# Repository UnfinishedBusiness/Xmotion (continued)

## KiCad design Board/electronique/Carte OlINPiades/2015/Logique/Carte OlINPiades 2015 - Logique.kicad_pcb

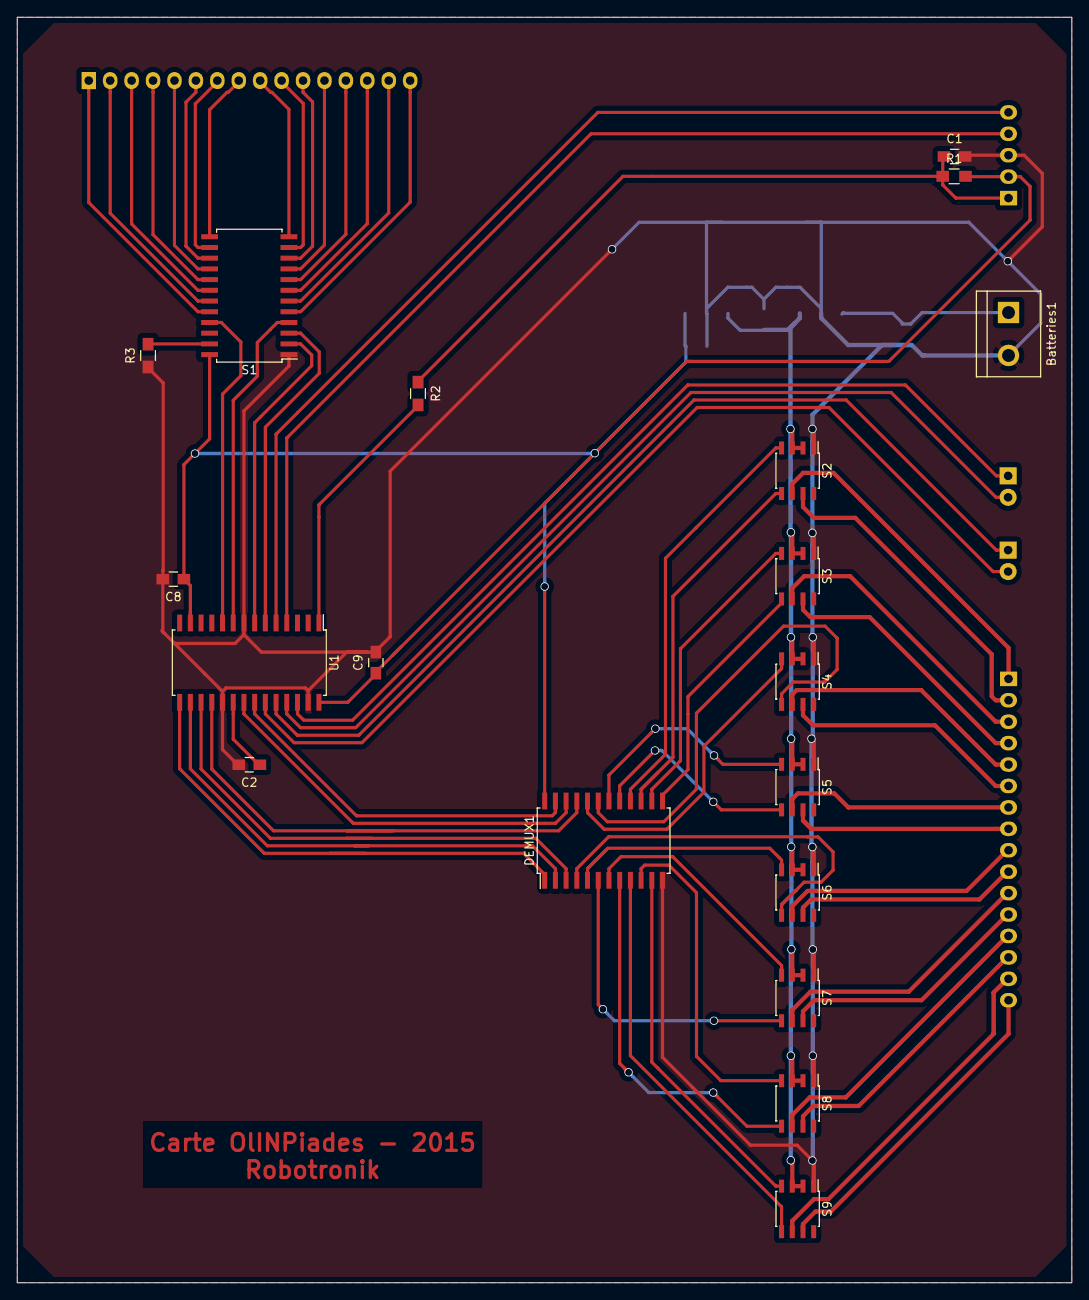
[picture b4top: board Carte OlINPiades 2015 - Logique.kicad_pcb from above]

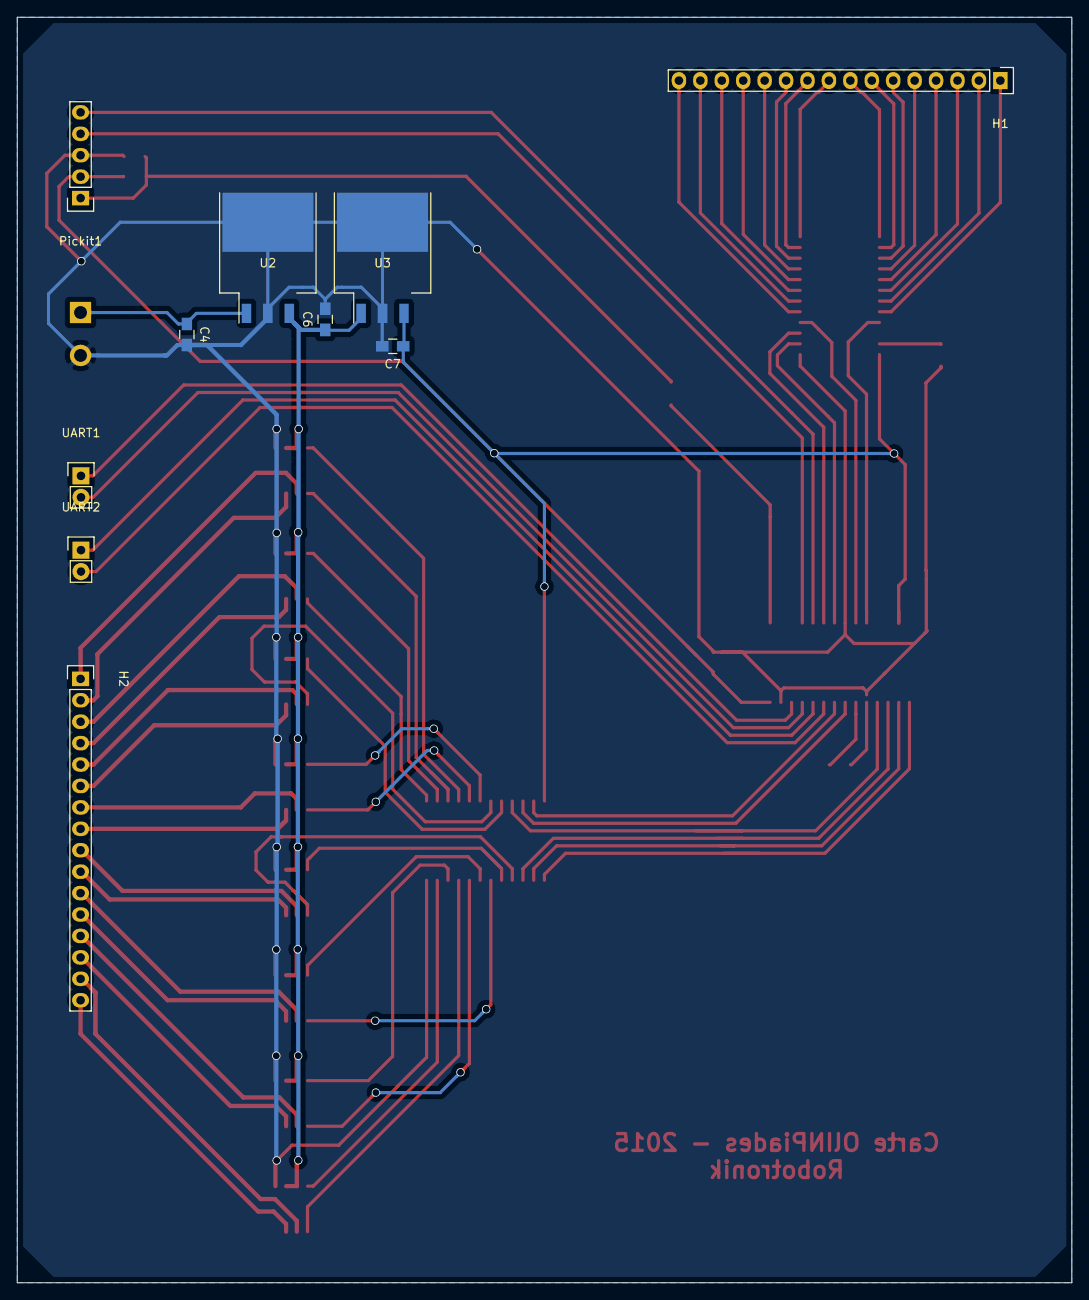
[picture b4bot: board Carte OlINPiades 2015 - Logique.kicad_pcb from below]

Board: 2 copper layers, 125.0 x 150.0 mm, 29 parts (10 on the bottom side), 72 nets.

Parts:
Batteries1: CONN_2; bornier2
C1, C6: 100nF; C_0805_HandSoldering
C2, C7: 10uF; C_0805_HandSoldering
C4: 330nF; C_0805_HandSoldering
C8, C9: 0,1uF; C_0805_HandSoldering
DEMUX1: 74HC4514; SOIC-24_7.5x15.4mm_Pitch1.27mm
H1, H2: PinHeader; Socket_Strip_Straight_1x16
Pickit1: CONN_5; Pin_Header_Straight_1x05
R1: 10kOhm; R_0805_HandSoldering
R2: 470Ohm; R_0805_HandSoldering
R3: TODO; R_0805_HandSoldering
S1: CAT4016; SOIC-24_7.5x15.4mm_Pitch1.27mm
S2, S3, S4, S5, S6, S7, S8, S9: TPS2080; SOIC-8_3.9x4.9mm_Pitch1.27mm
U1: dsPIC33FJ128MC802; SOIC-28_7.5x17.9mm_Pitch1.27mm
U2: 7805; TO-263
U3: LM2937-3.3; TO-263
UART1, UART2: CONN_2; Pin_Header_Straight_1x02

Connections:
+3.3V: C7.1, C8.1, C9.1, DEMUX1.24, Pickit1.2, R1.2, S1.24, U1.13, U1.28, U3.VO
+5V: C6.1, S2.2, S2.3, S3.2, S3.3, S4.2, S4.3, S5.2, S5.3, S6.2, S6.3, S7.2, S7.3, S8.2, S8.3, S9.2, S9.3, U2.VO, U3.VI
+12V: Batteries1.1, C4.1, U2.VI
GND: Batteries1.2, C1.2, C2.2, C4.2, C6.2, C7.2, C8.2, C9.2, DEMUX1.12, Pickit1.3, R3.1, S1.1, S2.1, S3.1, S4.1, S5.1, S6.1, S7.1, S8.1, S9.1, U1.8, U1.19, U1.27, U2.GND, U3.GND
unnamed: C1.1, Pickit1.1, R1.1, R2.1
unnamed: C2.1, U1.20
unnamed: DEMUX1.4, S6.5
unnamed: DEMUX1.5, S6.4
unnamed: DEMUX1.6, S7.5
unnamed: DEMUX1.7, S7.4
unnamed: DEMUX1.8, S8.5
unnamed: DEMUX1.9, S9.5
unnamed: DEMUX1.10, S8.4
unnamed: DEMUX1.11, S9.4
unnamed: DEMUX1.13, S3.5
unnamed: DEMUX1.14, S3.4
unnamed: DEMUX1.15, S2.5
unnamed: DEMUX1.16, S2.4
unnamed: DEMUX1.17, S5.5
unnamed: DEMUX1.18, S5.4
unnamed: DEMUX1.19, S4.5
unnamed: DEMUX1.20, S4.4
unnamed: H1.1, S1.20
unnamed: H1.2, S1.19
unnamed: H1.3, S1.18
unnamed: H1.4, S1.17
unnamed: H1.5, S1.16
unnamed: H1.6, S1.15
unnamed: H1.7, S1.14
unnamed: H1.8, S1.13
unnamed: H1.9, S1.12
unnamed: H1.10, S1.11
unnamed: H1.11, S1.10
unnamed: H1.12, S1.9
unnamed: H1.13, S1.8
unnamed: H1.14, S1.7
unnamed: H1.15, S1.6
unnamed: H1.16, S1.5
unnamed: H2.1, S2.6
unnamed: H2.2, S2.7
unnamed: H2.3, S3.6
unnamed: H2.4, S3.7
unnamed: H2.5, S4.6
unnamed: H2.6, S4.7
unnamed: H2.7, S5.6
unnamed: H2.8, S5.7
unnamed: H2.9, S6.6
unnamed: H2.10, S6.7
unnamed: H2.11, S7.6
unnamed: H2.12, S7.7
unnamed: H2.13, S8.6
unnamed: H2.14, S8.7
unnamed: H2.15, S9.6
unnamed: H2.16, S9.7
unnamed: R2.2, U1.1
unnamed: R3.2, S1.23
PGC: Pickit1.5, U1.5
PGD: Pickit1.4, U1.4
RA2: S1.4, U1.9
RA3: S1.21, U1.10
RB2: S1.3, U1.6
RB3: S1.2, U1.7
RB6: DEMUX1.1, U1.15
RB7: DEMUX1.2, U1.16
RB8: DEMUX1.3, U1.17
RB9: DEMUX1.21, U1.18
RB10: DEMUX1.22, U1.21
RB11: DEMUX1.23, U1.22
RB12: U1.23, UART2.2
RB13: U1.24, UART2.1
RB14: U1.25, UART1.2
RB15: U1.26, UART1.1

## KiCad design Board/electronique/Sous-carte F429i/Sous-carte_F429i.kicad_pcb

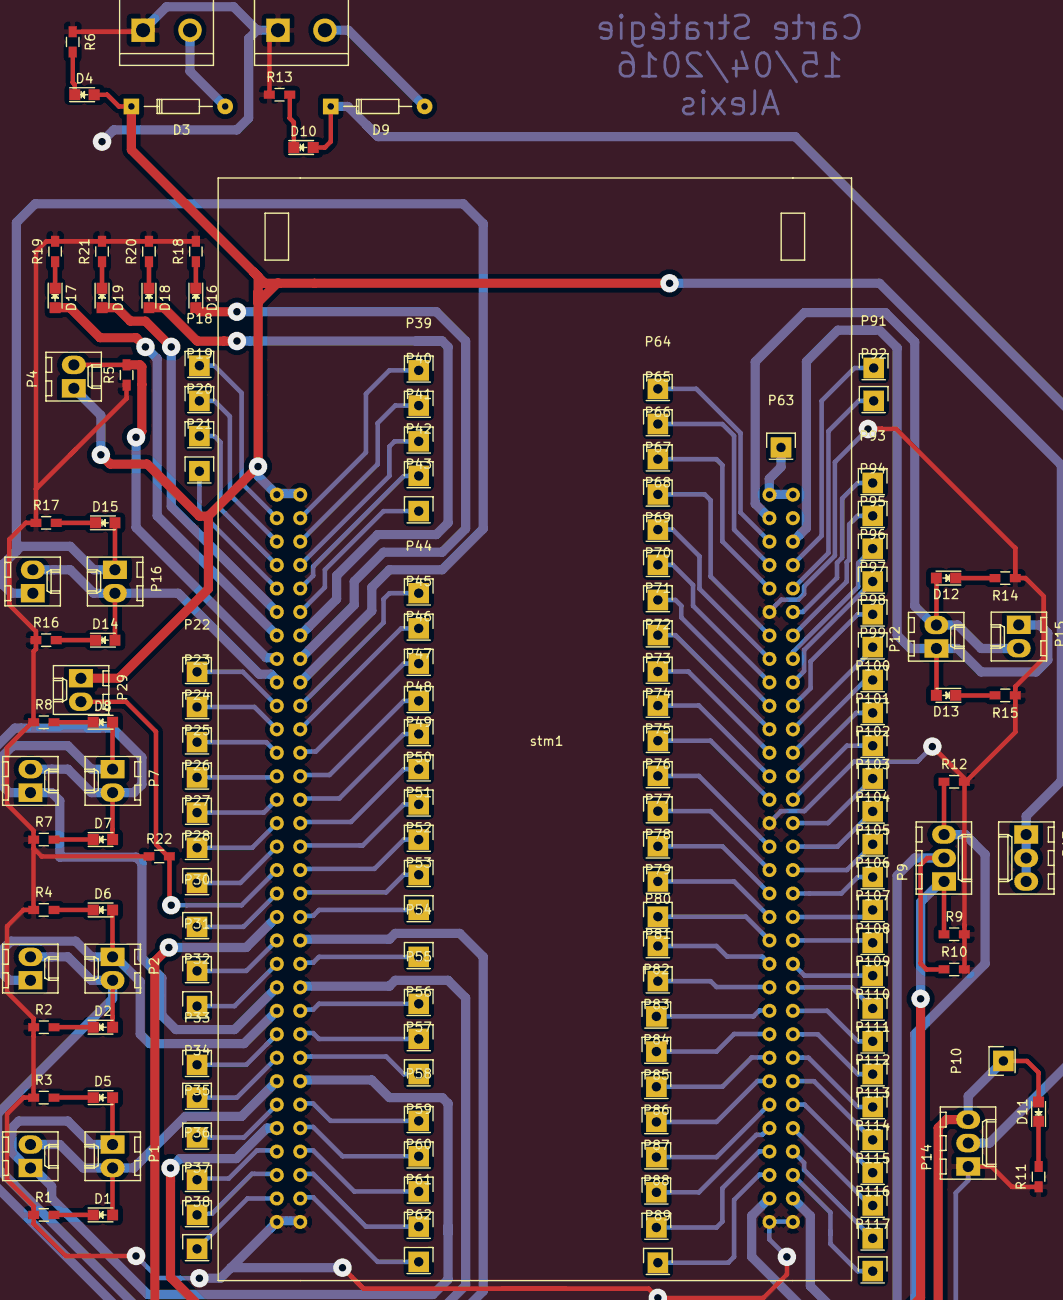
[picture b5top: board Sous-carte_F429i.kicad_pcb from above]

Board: 2 copper layers, 158 parts (0 on the bottom side), 140 nets.

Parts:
D1, D2, D4, D5, D6, D7, D8, D10, D11, D12, D13, D14, D15, D16, D17, D18, D19: LED; LED_0805
D3, D9: D; Diode_DO-35_SOD27_Horizontal_RM10
P1, P2, P4, P5, P6, P7, P8, P12, P15, P16, P17, P29: CONN_01X02; Molex_KK_6410-02
P3, P11: CONN_01X02; bornier2
P9, P13, P14: CONN_01X03; Molex_KK_6410-03
P10, P18, P19, P20, P21, P22, P23, P24, P25, P26, P27, P28, P30, P31, P32, P33, P34, P35, P36, P37, P38, P39, P40, P41, P42, P43, P44, P45, P46, P47, P48, P49, P50, P51, P52, P53, P54, P55, P56, P57, P58, P59, P60, P61, P62, P63, P64, P65, P66, P67, P68, P69, P70, P71, P72, P73, P74, P75, P76, P77, P78, P79, P80, P81, P82, P83, P84, P85, P86, P87, P88, P89, P91, P92, P93, P94, P95, P96, P97, P98, P99, P100, P101, P102, P103, P104, P105, P106, P107, P108, P109, P110, P111, P112, P113, P114, P115, P116, P117: CONN_01X01; Pin_Header_Straight_1x01
R1, R2, R3, R4, R5, R6, R7, R8, R9, R10, R11, R12, R13, R14, R15, R16, R17, R18, R19, R20, R21, R22: R; R_0603_HandSoldering
stm1: STM32F429i-Discovery; stm32f429i-disco

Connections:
+5V: D3.1, D4.2, P4.1, P13.1, P13.2, P13.3, P29.1, stm1.1, stm1.2
+BATT: D9.1, D10.2, P14.2
EQUIPE: P29.2, R22.2, stm1.33
GND: P3.1, P11.1, P14.1, R1.1, R2.1, R3.1, R4.1, R5.1, R6.1, R7.1, R8.1, R9.2, R10.2, R11.1, R12.2, R13.1, R14.1, R15.1, R16.1, R17.1, R18.2, R19.2, R20.2, R21.2, R22.1, stm1.63, stm1.64, stm1.75, stm1.93, stm1.127, stm1.128
LED_1: D16.2, stm1.16
LED_2: D17.2, stm1.13
LED_3: D18.2, stm1.14
LED_4: D19.2, stm1.11
unnamed: D1.1, R1.2
unnamed: D2.1, R2.2
unnamed: D3.2, P3.2
unnamed: D4.1, R6.2
unnamed: D5.1, R3.2
unnamed: D6.1, R4.2
unnamed: D7.1, R7.2
unnamed: D8.1, R8.2
unnamed: D9.2, P11.2
unnamed: D10.1, R13.2
unnamed: D11.1, R11.2
unnamed: D12.1, R14.2
unnamed: D13.1, R15.2
unnamed: D14.1, R16.2
unnamed: D15.1, R17.2
unnamed: D16.1, R18.1
unnamed: D17.1, R19.1
unnamed: D18.1, R20.1
unnamed: D19.1, R21.1
unnamed: P18.1, stm1.3
unnamed: P19.1, stm1.5
unnamed: P20.1, stm1.7
unnamed: P21.1, stm1.9
unnamed: P22.1, stm1.19
unnamed: P23.1, stm1.21
unnamed: P24.1, stm1.23
unnamed: P25.1, stm1.25
unnamed: P26.1, stm1.27
unnamed: P27.1, stm1.29
unnamed: P28.1, stm1.31
unnamed: P30.1, stm1.35
unnamed: P31.1, stm1.39
unnamed: P32.1, stm1.41
unnamed: P33.1, stm1.47
unnamed: P34.1, stm1.49
unnamed: P35.1, stm1.53
unnamed: P36.1, stm1.57
unnamed: P37.1, stm1.59
unnamed: P38.1, stm1.61
unnamed: P39.1, stm1.4
unnamed: P40.1, stm1.6
unnamed: P41.1, stm1.8
unnamed: P42.1, stm1.10
unnamed: P43.1, stm1.12
unnamed: P44.1, stm1.20
unnamed: P45.1, stm1.22
unnamed: P46.1, stm1.24
unnamed: P47.1, stm1.26
unnamed: P48.1, stm1.28
unnamed: P49.1, stm1.30
unnamed: P50.1, stm1.32
unnamed: P51.1, stm1.34
unnamed: P52.1, stm1.36
unnamed: P53.1, stm1.38
unnamed: P54.1, stm1.42
unnamed: P55.1, stm1.46
unnamed: P56.1, stm1.48
unnamed: P57.1, stm1.50
unnamed: P58.1, stm1.54
unnamed: P59.1, stm1.56
unnamed: P60.1, stm1.58
unnamed: P61.1, stm1.60
unnamed: P62.1, stm1.62
unnamed: P63.1, stm1.65, stm1.66
unnamed: P64.1, stm1.69
unnamed: P65.1, stm1.71
unnamed: P66.1, stm1.73
unnamed: P67.1, stm1.77
unnamed: P68.1, stm1.79
unnamed: P69.1, stm1.81
unnamed: P70.1, stm1.83
unnamed: P71.1, stm1.85
unnamed: P72.1, stm1.87
unnamed: P73.1, stm1.89
unnamed: P74.1, stm1.91
unnamed: P75.1, stm1.95
unnamed: P76.1, stm1.97
unnamed: P77.1, stm1.99
unnamed: P78.1, stm1.101
unnamed: P79.1, stm1.103
unnamed: P80.1, stm1.105
unnamed: P81.1, stm1.107
unnamed: P82.1, stm1.109
unnamed: P83.1, stm1.111
unnamed: P84.1, stm1.113
unnamed: P85.1, stm1.115
unnamed: P86.1, stm1.117
unnamed: P87.1, stm1.119
unnamed: P88.1, stm1.121
unnamed: P89.1, stm1.123
unnamed: P91.1, stm1.72
unnamed: P92.1, stm1.74
unnamed: P93.1, stm1.76
unnamed: P94.1, stm1.78
unnamed: P95.1, stm1.80
unnamed: P96.1, stm1.82
unnamed: P97.1, stm1.84
unnamed: P98.1, stm1.86
unnamed: P99.1, stm1.88
unnamed: P100.1, stm1.90
unnamed: P101.1, stm1.92
unnamed: P102.1, stm1.94
unnamed: P103.1, stm1.96
unnamed: P104.1, stm1.98
unnamed: P105.1, stm1.100
unnamed: P106.1, stm1.102
unnamed: P107.1, stm1.104
unnamed: P108.1, stm1.106
unnamed: P109.1, stm1.108
unnamed: P110.1, stm1.110
unnamed: P111.1, stm1.112
unnamed: P112.1, stm1.114
unnamed: P113.1, stm1.116
unnamed: P114.1, stm1.118
unnamed: P115.1, stm1.120
unnamed: P116.1, stm1.122
unnamed: P117.1, stm1.124
START: P4.2, R5.2, stm1.15
SWITCH_0: P9.1, R9.1, stm1.55
SWITCH_1: P9.2, R10.1, stm1.126
SWITCH_2: P9.3, R12.1, stm1.125
UART4_RX: D2.2, P2.2, P6.2, stm1.44
UART4_TX: D6.2, P2.1, P6.1, stm1.45
UART5_RX: D7.2, P7.2, P8.2, stm1.40
UART5_TX: D8.2, P7.1, P8.1, stm1.43
UART7_RX: D12.2, P12.2, P15.2, stm1.67
UART7_TX: D13.2, P12.1, P15.1, stm1.70
UART8_RX: D14.2, P16.2, P17.2, stm1.17
UART8_TX: D15.2, P16.1, P17.1, stm1.18
USART1_RX: D1.2, P1.2, P5.2, stm1.51
USART1_TX: D5.2, P1.1, P5.1, stm1.52
USART2_TX: D11.2, P10.1, P14.3, stm1.37

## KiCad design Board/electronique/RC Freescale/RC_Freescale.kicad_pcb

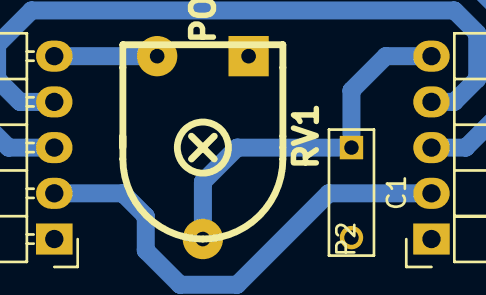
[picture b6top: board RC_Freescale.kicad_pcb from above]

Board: 2 copper layers, 4 parts (0 on the bottom side), 6 nets.

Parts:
C1: C; C_Rect_L7_W2.5_P5
P1: CONN_01X05; Pin_Header_Angled_1x05
P2: CONN_01X05; Socket_Strip_Angled_1x05
RV1: POT; POAH

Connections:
/2: P1.2, P2.2
/3: P1.3, P2.3
/4: P1.4, P2.4
GND: C1.2, P1.1, P2.1
unnamed: C1.1, P2.5, RV1.2
unnamed: P1.5, RV1.3

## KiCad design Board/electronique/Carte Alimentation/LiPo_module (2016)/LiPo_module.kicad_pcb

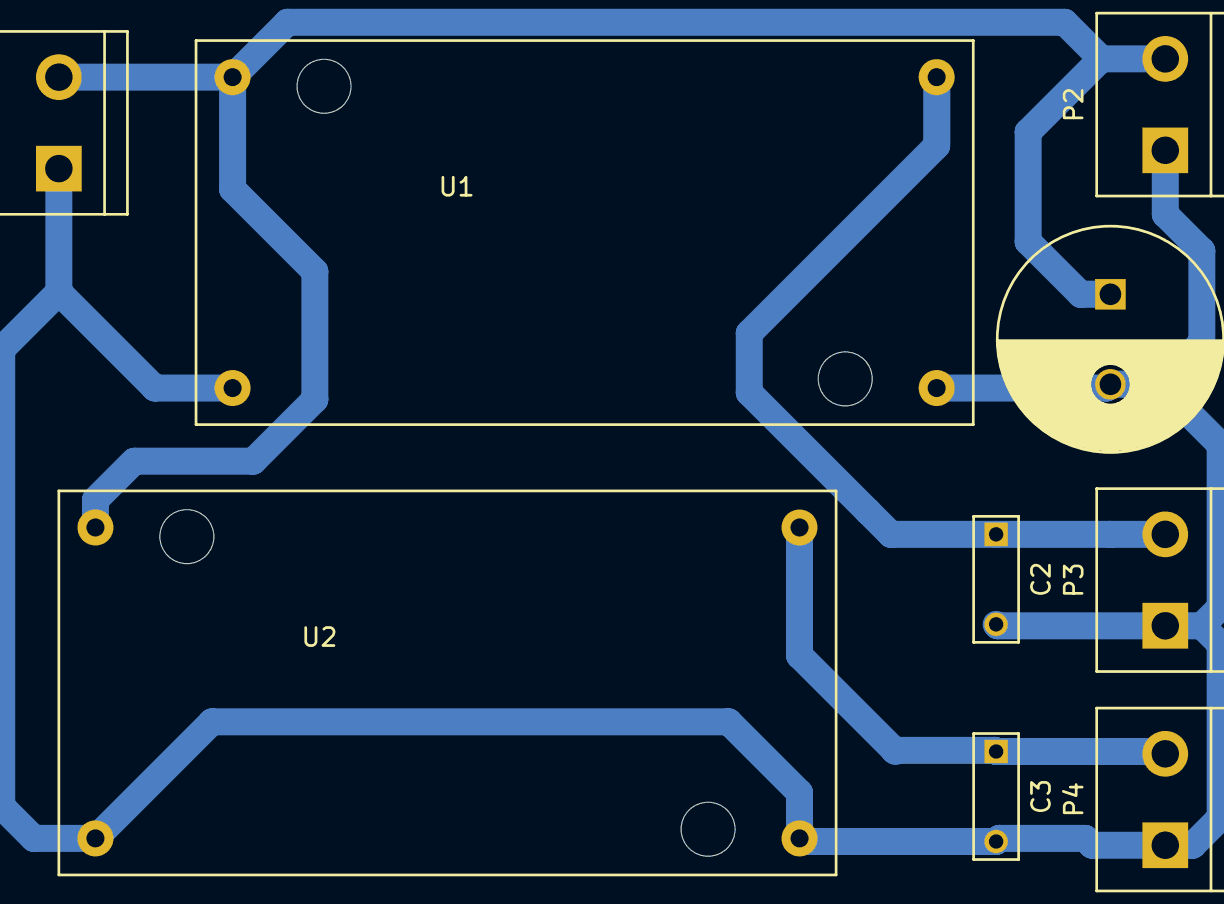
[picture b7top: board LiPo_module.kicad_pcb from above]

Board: 2 copper layers, 9 parts (0 on the bottom side), 4 nets.

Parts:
C1: CP; C_Radial_D12.5_L25_P5
C2, C3: C; C_Rect_L7_W2.5_P5
P1, P2, P3, P4: CONN_01X02; bornier2
U1, U2: DSN2596

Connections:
GND: C1.2, C2.2, C3.2, P1.1, P2.1, P3.1, P4.1, U1.2, U1.3, U2.2, U2.3
unnamed: C1.1, P1.2, P2.2, U1.1, U2.1
unnamed: C2.1, P3.2, U1.4
unnamed: C3.1, P4.2, U2.4

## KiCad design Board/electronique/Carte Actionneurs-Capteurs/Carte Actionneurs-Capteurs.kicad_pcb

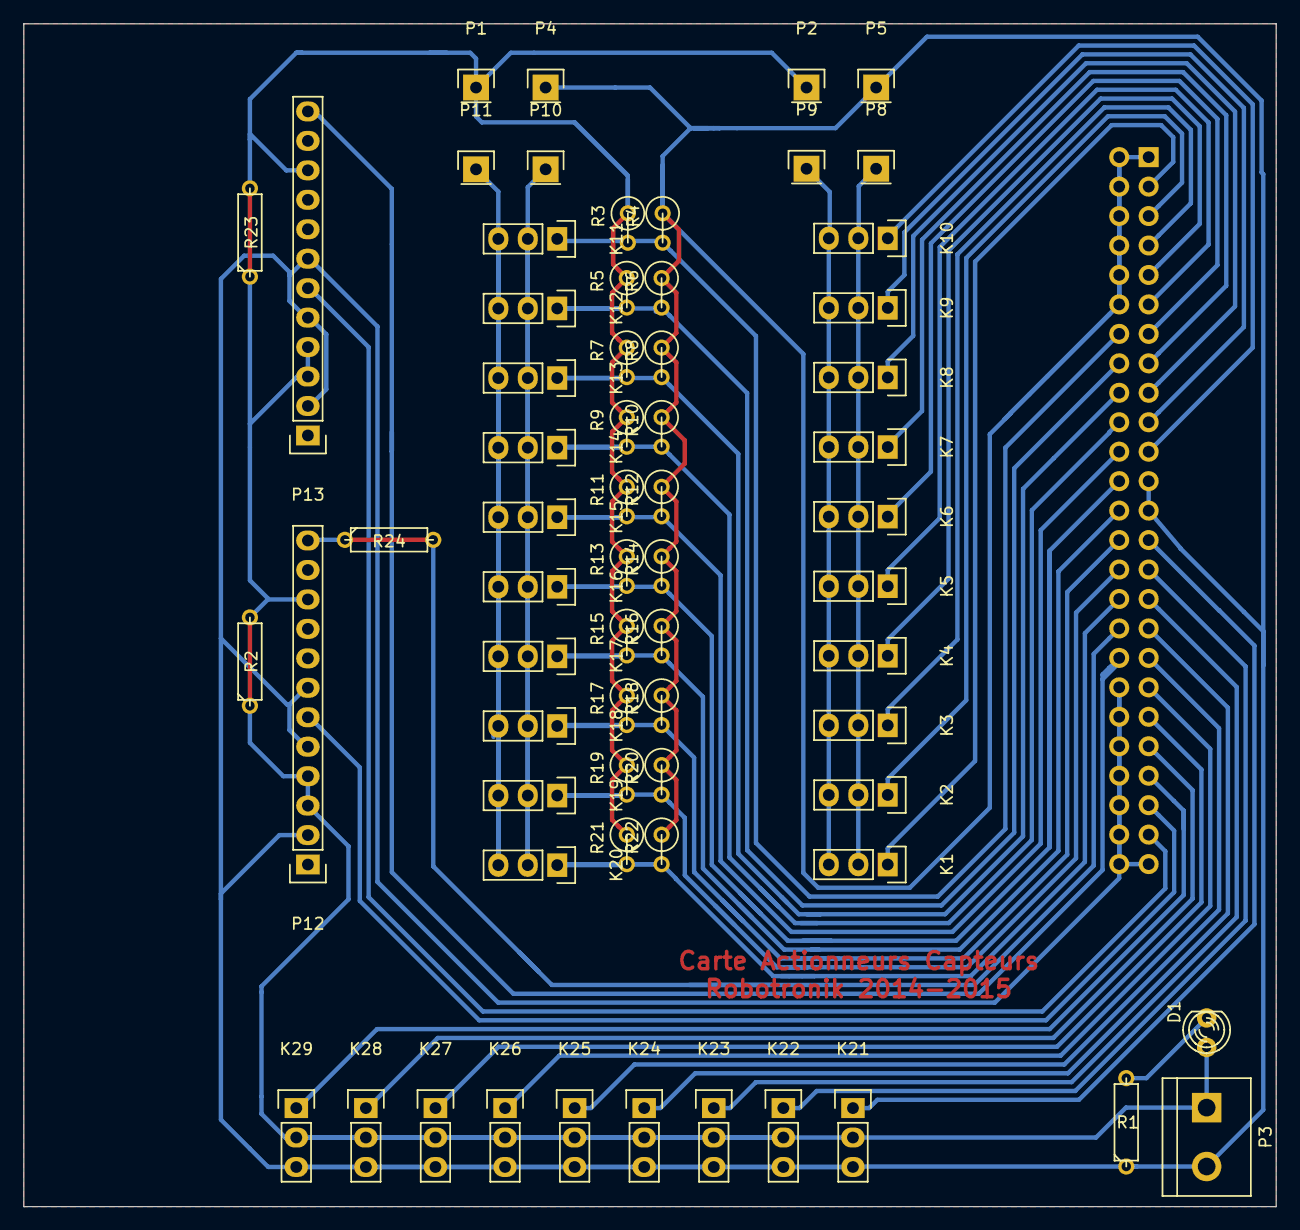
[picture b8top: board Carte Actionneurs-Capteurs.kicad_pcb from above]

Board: 2 copper layers, 108.0 x 102.0 mm, 66 parts (1 on the bottom side), 40 nets.

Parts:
D1: LED; LED-3MM
K1, K2, K3, K4, K5, K6, K7, K8, K9, K10, K11, K12, K13, K14, K15, K16, K17, K18, K19, K20, K21, K22, K23, K24, K25, K26, K27, K28, K29: CONN_01x03; Pin_Header_Straight_1x03
P1, P2, P4, P5, P8, P9, P10, P11: CONN_1; Pin_Header_Straight_1x01
P3: CONN_2; bornier2
P6: CONN_25X2; Pin_Header_Straight_2x25
P12, P13: CONN_12; Pin_Header_Straight_1x12
R1, R2, R23, R24: R; R3
R3, R4, R5, R6, R7, R8, R9, R10, R11, R12, R13, R14, R15, R16, R17, R18, R19, R20, R21, R22: R; R1

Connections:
ADC1: K1.1, P6.3
ADC2: K2.1, P6.5
ADC3: K3.1, P6.7
ADC4: K4.1, P6.9
ADC5: K5.1, P6.11
ADC6: K6.1, P6.13
ADC7: K7.1, P6.15
ADC8: K8.1, P6.17
ADC9: K9.1, P6.19
ADC10: K10.1, P6.21
IO1: K11.1, P6.14, R3.2, R4.2
IO2: K12.1, P6.16, R5.2, R6.2
IO3: K13.1, P6.18, R7.2, R8.2
IO4: K14.1, P6.20, R9.2, R10.2
IO5: K15.1, P6.22, R11.2, R12.2
IO6: K16.1, P6.24, R13.2, R14.2
IO7: K17.1, P6.26, R15.2, R16.2
IO8: K18.1, P6.28, R17.2, R18.2
IO9: K19.1, P6.30, R19.2, R20.2
IO10: K20.1, P6.32, R21.2, R22.2
IO11: P6.34, P12.12, R24.1, R24.2
IO12: P6.36, P13.12
unnamed: D1.2, R1.2
PWM1: K21.1, P6.27
PWM2: K22.1, P6.29
PWM3: K23.1, P6.31
PWM4: K24.1, P6.33
PWM5: K25.1, P6.35
PWM6: K26.1, P6.37
PWM7: K27.1, P6.39
PWM8: K28.1, P6.41
PWM9: K29.1, P6.43
PWM10: P6.45, P12.6
PWM11: P6.47, P13.6
PWR_ADC_1: K1.2, K2.2, K3.2, K4.2, K5.2, K6.2, K7.2, K8.2, K9.2, K10.2, P8.1
PWR_ADC_2: K1.3, K2.3, K3.3, K4.3, K5.3, K6.3, K7.3, K8.3, K9.3, K10.3, P9.1
PWR_ADC_3: D1.1, K21.2, K22.2, K23.2, K24.2, K25.2, K26.2, K27.2, K28.2, K29.2, P1.1, P2.1, P3.1, P12.3, P12.4, P12.10, P13.3, P13.4, P13.10, R2.1, R2.2, R3.1, R5.1, R7.1, R9.1, R11.1, R13.1, R15.1, R17.1, R19.1, R21.1, R23.1, R23.2
PWR_ADC_4: K21.3, K22.3, K23.3, K24.3, K25.3, K26.3, K27.3, K28.3, K29.3, P3.2, P4.1, P5.1, P6.1, P6.2, P6.4, P6.6, P6.8, P6.10, P6.12, P6.23, P6.25, P6.38, P6.40, P6.42, P6.44, P6.46, P6.48, P6.49, P6.50, P12.2, P12.5, P12.7, P13.2, P13.5, P13.7, R1.1, R4.1, R6.1, R8.1, R10.1, R12.1, R14.1, R16.1, R18.1, R20.1, R22.1
PWR_IO_1: K11.2, K12.2, K13.2, K14.2, K15.2, K16.2, K17.2, K18.2, K19.2, K20.2, P10.1
PWR_IO_2: K11.3, K12.3, K13.3, K14.3, K15.3, K16.3, K17.3, K18.3, K19.3, K20.3, P11.1

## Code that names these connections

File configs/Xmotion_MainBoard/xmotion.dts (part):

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
	/* ------ STEPPERS ------ */

		"P8.12",	/* gpio1.12  #X_STEP */
		"P8.11",	/* gpio1.13  #X_DIR */
		"P8.16",	/* gpio1.14  #y1_step */
		"P8.15",	/* gpio1.15  #y1_dir */
		"P9.15",	/* gpio1.16  #Z_STEP */
		"P9.23",	/* gpio1.17  #Z_DIR */
		"P9.22",	/* gpio0.2   #y2_STEP */
		//"P9.21",	/* gpio0.3   #y2_dir */
		"P9.18",	/* gpio0.2   #A_STEP */
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					status = "okay";
					pinctrl-single,pins = <
						/* stepper outputs */
						0x030 0x07	/* #X_STEP, P8_12, gpio1.12, mode7 out */
						0x034 0x07	/* #X_DIR, P8_11, gpio1.13, mode7 out */

						0x038 0x07	/* #y1_step, P8_16, gpio1.14, mode7 out */
						0x03c 0x07	/* #y1_dir, P8_15, gpio1.15, mode7 out */

						0x040 0x07	/* #Z_STEP, P9_15, gpio1.16, mode7 out */
						0x044 0x07	/* #Z_DIR, P9_23, gpio1.17, mode7 out */

						0x150 0x07	/* #y2_STEP, P9_22, gpio0.2,  mode7 out */
						0x154 0x07	/* #y2_dir, P9_21, gpio0.3,  mode7 out */
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					pinctrl-0 = <&xmotion_stepper_pins>;

					x_step {
						gpio-name = "xmotion:x_step";
						gpio = <&gpio2 12 0>;
						output;
						init-low;
					};
					x_dir {
						gpio-name = "xmotion:x_dir";
						gpio = <&gpio2 13 0>;
						output;
						init-low;
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						init-low;
					};
					z_step {
						gpio-name = "xmotion:z_step";
						gpio = <&gpio2 16 0>;
						output;
						init-low;
					};
					z_dir {
						gpio-name = "xmotion:z_dir";
						gpio = <&gpio2 17 0>;
						output;
						init-low;
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
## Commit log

2016-05-09 Got part of ui done
2016-05-10 Got simple servo class working
2016-05-10 Got servo jog working
2016-05-11 Got Motion control about buttoned up
2016-05-11 Got Gcode parser working
2016-05-11 Fixed huge memory leak and add signal handler for clean exit
2016-05-11 Implemented seperate thread for CNC
2016-05-12 Got Rapid line interpelation
2016-05-12 Wrapped up lines and rapids, time for circles
2016-05-12 arcs are being fucking worthless cock suckers
2016-05-12 sketchy commit, i think i just interpolated an arc
2016-05-13 fucking stupid whore
2016-05-14 Finished motion accel
2016-06-11 Started working on circuit board
2016-06-11 Board is ready to route
2016-06-11 Plotted PCB
2016-06-15 Fucking pissing me off
2016-06-15 Finally got a posted toolpath to work
2016-06-15 Need to make symbol parsing dynamic by key not array position
2016-06-16 I hate math, but everything is working here
2016-06-16 funny stuff, fixed another bug were big arcs ran away
2016-06-16 Passed letter test
2016-06-17 Figured out better way to calculate arc endpoint
2016-06-17 Fixed arc endpoint detection that I previously thought I had rapped up
2016-06-17 added step_test.c
2016-06-17 Added stepper motor datasheet
2016-06-17 got a stepper working
2016-06-17 Done testing!
2016-06-17 Implemented axis drivers
2016-06-17 Added speed test!
2016-06-18 Added file menu
2016-06-18 Slowed down rapid feed rate
2016-06-18 Added poweroff button
2016-06-18 Actually got it working mostly on the machine
2016-06-18 Build mod board to mosfet wiring error
2016-06-18 Added arc micro line filter to avoid micro follower error
2016-06-18 Added dwell to cutting head
2016-06-24 Fixed arc endpoint issue
2016-06-26 Fixed errors made in first revision and plotted
2016-06-26 Fixed multiple start cutting delay
2016-06-27 Maybe fixed feedrate issue
2016-06-27 Added scrolling to FileOpen activity
2016-06-28 Adjusted rapid feed rate
2016-07-05 Maybe solved engine moiunt runaway, but could not reproduce in debug
2016-07-22 Added non modal gcode support
2016-07-22 Fixed full circle bug
2016-07-24 Added some gcode implovements
2016-07-25 Changed to 1/8 steps
2016-07-26 Completly ignores feedrate
2016-07-26 Added some ui stuff
2016-07-26 Added Z axis
2016-07-26 Fuckit, im just gonna use this for the hmi and send gcode to grbl
2016-07-28 Jerked out all the motion control
2016-07-28 Finally get consistend serial data from controller
2016-07-28 I fucking hate everythinggit add --allgit add --all
2016-07-28 This is fucking rediculous
2016-07-29 The trick to the serial read semas to be an ioctl to get data thats ready to be read
2016-07-30 Got a program to run
2016-07-30 Got non blocking sender working
2016-07-30 Works but automaticly restarts file for some reason
2016-07-30 Works unless i turn on machine position feedback
2016-07-30 Seemed to have solved sender bugs
2016-07-30 Added z origin buttons
2016-07-30 Added stop latch so program cant auto restart
2016-07-30 Still some strange sender bugs but I have to move on to other thinks
2016-07-30 Fixed a bug in serial
2016-07-30 Removed sdl destroy texture
2016-07-30 Trying to solve wierd texture blank on pi
2016-07-30 fucning [fsdafdsa[fsad
2016-07-30 Maybe solved hold start bug
2016-07-31 Still trying to solve blob issue
2016-07-31 Maybe fixed memory leak
2016-07-31 Turned on optimations
2016-07-31 There seems to be a minor stack overflow somewere
2016-09-02 Updated shematic to hopefully protect from hf
2016-09-03 Finished cvpcb
2016-09-04 Got board layed out
2016-09-04 Locked down board layout
2016-09-04 Just about finished routing
2016-09-04 Finished Roughting
2016-09-05 Plotted and archived
2016-09-06 Updated BOM
2016-09-07 Finished bottom side of enclosure and submitted to be made
2016-09-27 Cleaned up and rename to Xmotion
2016-09-27 Deleted trash directory
2017-08-30 Finished Schematic Design
2017-08-31 Board is layed out
2017-09-01 Board is routed
2017-09-01 Routing is finished
2017-09-01 Subbmitted to fab house
2017-11-06 Updated Schematic, fixed pinmap to work with Mesa 5i25 G540 Firmware and added opto-isolators
2017-11-07 Board is ready to be routed
2017-11-08 Started Routing board
2017-11-10 Ready to fabricate second revision
2017-11-11 Fixed Fill issue, luckily previous commit did not pass audit
2018-09-06 We have a working framebuffer ui with keyboard input
2018-09-06 Have a demo up and running, no keyboard and mouse yet
2018-09-07 Mouse is working and keyboard driver is nearly finished
2018-09-09 GUI is coming together
2018-09-10 System has been duty sim tested for a ton of hours and no issues so far
2018-09-11 Started working on LinuxCNC intigration
2018-09-11 Jogging works
2018-09-11 DRO works
2018-09-12 Figured out how to interface to linuxcnc nml via python
2018-09-12 Controls work, Homing only works if numbers are positive. Set 0 buttons don't work right yet
2018-09-13 Got quirky homing figured out
2018-09-14 Added config_example.ini
2018-09-14 Switched from old way to read mouse to new event way so we can read scroll up and down
2018-09-14 It's being a whore
2018-09-15 Gonna have to switch to sdt:vector, can't seem to nail down the pointer mayham
2018-09-15 Upgraded to cpp in elements to make use of vectors for viewer entitiy array
2018-09-15 Got viewer bugs worked out
2018-09-15 DRO is now pure c
2018-09-16 Added headers that would normaly be installed at /usr/includes/linuxcnc/ to machinekit_headers. Won't make, complains about all kinds of stupid shit
2018-09-16 Removed lv_examples and did some testing on the embedded platform
2018-09-16 Viewer stack finally passes 10,000 entity test.
2018-09-16 Seperated ui elements into seperate sources
2018-09-16 gcode parse is templated out
2018-09-17 Gcode parser is working
2018-09-17 Gcode parser should be ready to interaface to the nc viewer
2018-09-17 Viewer displays line moves
2018-09-18 Shoehorned ProfileCAD's geometry library into the system so I could draw arcs. Will probably be stripped later in favior of JetCad's Javascript based Geometry Engine
2018-09-18 Viewer arc drawing works but arc drawing enpoints are really bugy, needs to be fixed but moving on to other things for the time being
2018-09-19 Started working on JetCad integration
2018-09-19 Got Maker.js working with Duktape
2018-09-21 We have an open dialog
2018-09-21 We can now open programs from the 'open' button
2018-09-22 Arc drawing is nailed down, stripped geometry library to the bare minimum and solved a core trig bug. Should be ready to intigrate JetCad now
2018-09-22 Fixed open dialog transparent button press wierdness
2018-09-22 Added a redraw flag to viewer
2018-09-22 Working on how jetcad will be integrated
2018-09-23 Fixed anoying keyboard input on tty while rendering to Framebuffer
2018-09-24 Added text_mode to reset tty if program dies before un-init
2018-09-24 Viewer is wcs aware now
2018-09-24 We can now run a program
2018-09-24 Added make sim so we can run gui withouth linuxcnc rtapi running
2018-09-24 Added DXF directory and a sample dxf
2018-09-24 Fixed SIM build
2018-09-24 Clean build, pre-hook added
2018-09-24 Viewer now scrolls to mouse
2018-09-25 Added viewer crosshair move into duty sim
2018-09-25 Added DRO color change when machine is homed
2018-09-25 Added .gitignore for build and bin directories
2018-09-25 Commit with build cleaned
2018-09-25 Added line to .gitignore
2018-09-25 Added .gitignore for dumb mac files
2018-09-25 Forgot a ignore for another dumb mac file
2018-09-25 Added mouse driver scroll callback and open dialog can now change paths
2018-09-25 Updated TODO.md
2018-09-26 Added ABS text onto DRO
2018-09-27 Fixed bug that was causing drawings to open really slow due to accidentally iterating through entites exponentially
2018-09-27 Viewer clipping algorythm works but is shotty
2018-09-27 Tweeked screen refresh rate and main cycle, need to figure out a priority based tasker
2018-09-27 This commit is broken, offloading everything but drawing to another thread works great for a bit then segfaults
2018-09-27 Fixed bug in terminal backspace
2018-09-27 Disabled viewer out of bounds clipper because slowdown when zoomed is not really an issue with multi-threaded input loops
2018-09-27 Added redraw on motion
2018-09-28 Fixed bug in dro_sim that was occasionally updating the dro labels from the second thread while the main thread was writing a different value, caused segfault
2018-09-28 Added Clock and started on Cycle timer element
2018-09-28 Knocking out TODO list items in order
2018-09-28 NC Control buttons now have groups for buttons that should stay toggled, like torch on or off
2018-09-28 Message box is kicking my ass
2018-09-28 Figured out msgbox bug, had a label object declared as static
2018-09-30 Knocking down TODO items
2018-10-07 Automatic keyboard device detection now works
2018-10-07 Mouse device detection is now automatic
2018-10-07 Added options to open dialog element
2018-10-08 Added ctrl-alt-F2 to switch to VT2 while in ui
2018-10-08 Added License.md
2018-10-08 Updated readme.md again
2018-10-08 Added javascript virtual machine and automatic javascript module loading
2018-10-10 Fixed edit bug
2018-10-10 Added javascript bindings for UI elements. UI is now being constructed and deconstructed from javascript so UI's can be easily designed for any purpose
2018-10-19 Made some hackish changes so it builds on Beagle Bone Machinekit binary image which has includes missing in /usr/includes...
2018-10-19 Made some changes to Xmotion_MainBoard config
2018-10-19 Added machinekit libs to extras
2018-10-19 Added liblinuxcnc.a because its missing in machinekit image
2018-10-19 Removed all libnml and liblinuxcnc stuff from linuxcnc.cpp
2018-10-20 Removed native C NML methods and switched them out for the python interface so everything works with machinekit withouth all this screwing around
2018-10-20 Fixed viewer redraw flag on status poll
2018-10-20 Fixed error channel
2018-10-20 Fixed slow indicators
2018-10-20 Estop works
2018-10-20 All digital inputs work
2018-10-21 Fixed memory leak
2018-10-21 Fixed another memory leak
2018-10-21 Okay, Think this is the last memory leak
2018-10-22 Added a script that will call the Xmotion binary as root even when machinekit is called as user machinekit, because machinekit can't be ran as root...
2018-10-29 Commit before adding pwm to Xmotion_MainBoard config
2018-11-05 Updated Xmotion_MainBoard config
2018-11-08 Fixed 1111 error when jogging with terminal open
2018-11-08 Added a signal catch, which should switch back to ktextmode if a segfault occurs
2018-11-08 Contrained mouse to screen boundry
2018-11-08 Added a max_viewer_entities cap
2018-11-09 Changed to 16bps temperarily for embeded system. Need to make this configurable at run time via config.ini
2018-11-12 Updated Config for Xmotion.ini
2018-11-12 Made some tweaks so automatic homing working correctly
2018-11-12 Added homing parameter to bump square gantry
2018-11-16 Slowed Down Y Velocity in Config for OffContact, Will be creating a branch for their machine soon
2018-12-10 Changed Drivers in OffContact router so we can get higher rapids
2018-12-10 Added debouncing to fix estop and probe inpu from floating while spindle was running
